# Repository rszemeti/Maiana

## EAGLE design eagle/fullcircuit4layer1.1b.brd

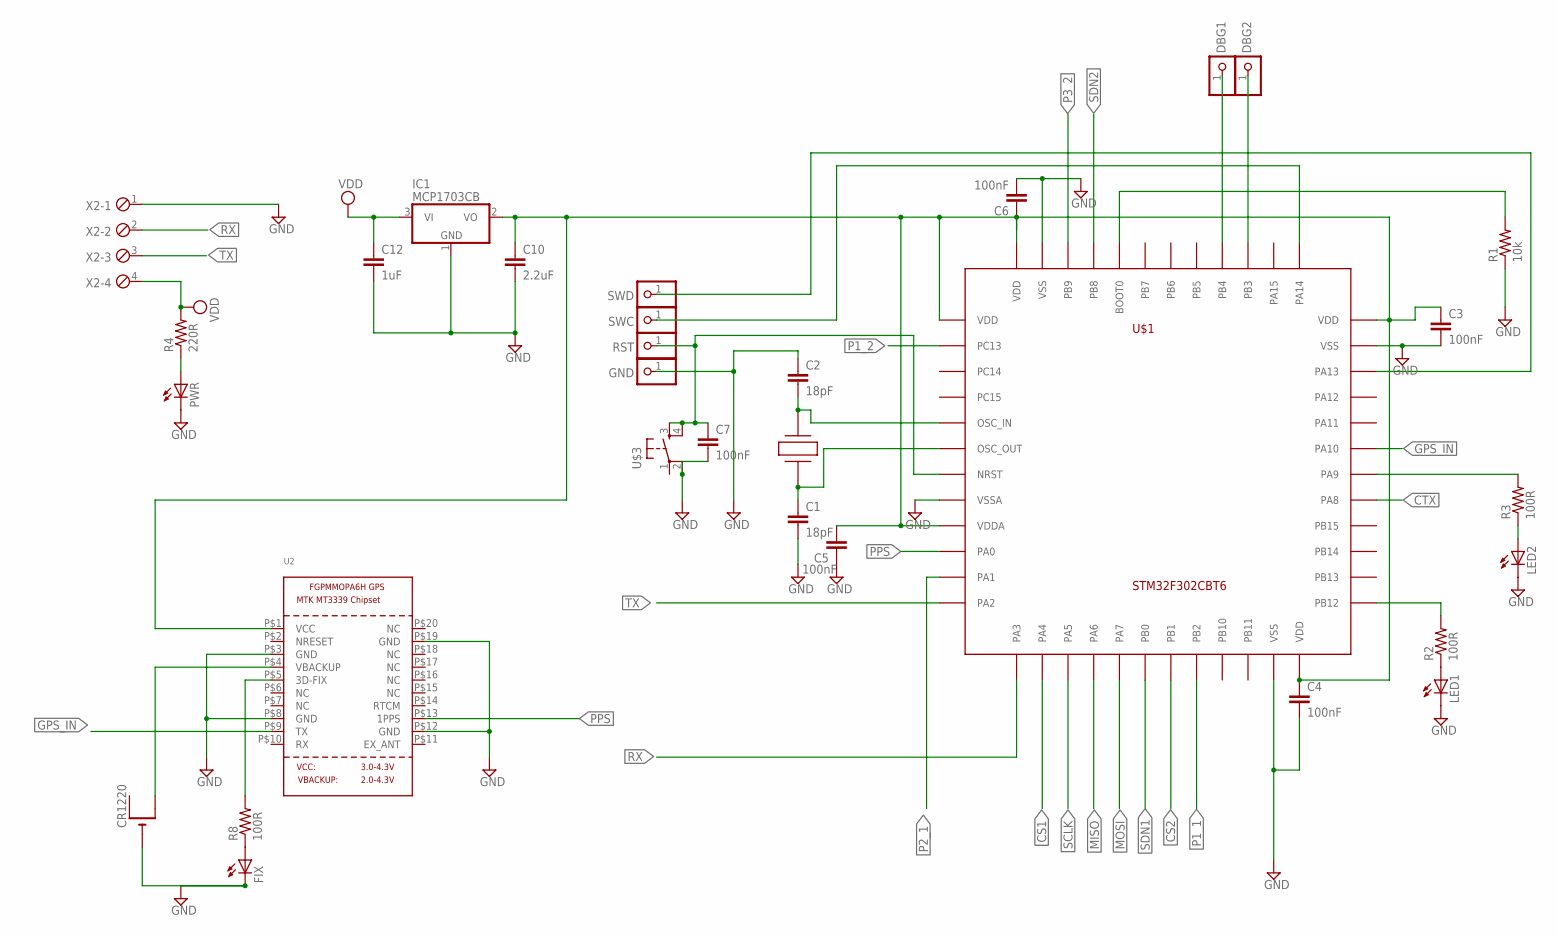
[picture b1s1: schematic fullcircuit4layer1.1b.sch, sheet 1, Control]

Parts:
C1, C2: 18pF; 0603-CAP
C3, C4, C5, C6, C7: 100nF; 0603-CAP
C10: 2.2uF; 0805
C12: 1uF; 0603-CAP
CR1220: CR1220SMT; CR1220-SMD
DBG1, DBG2: PINHD-1X1; 1X01
FIX: LEDCHIP-LED0603; CHIP-LED0603
GND: PINHD-1X1; 1X01
IC1: MCP1703CB; SOT23
LED1, LED2: LEDCHIP-LED0603; CHIP-LED0603
PWR: LEDCHIP-LED0603; CHIP-LED0603
R1: 10k; 0603-RES
R2, R3, R8: 100R; 0603-RES
R4: 220R; 0603-RES
RST: PINHD-1X1; 1X01
SWC: PINHD-1X1; 1X01
SWD: PINHD-1X1; 1X01
U2: GPS_FGPMMOPA6H; FGPMMOPA6H
U$1: STM32F302CBT6; LQFP48
U$3: TACTILE-SWITCH-7914G; 7914G
X1: TXC_7A
X2: MPT4; 4POL254

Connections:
CS1: U$1.P$14 (PA4); also elsewhere on the board
CS2: U$1.P$19 (PB1); also elsewhere on the board
CTX: U$1.P$29 (PA8); also elsewhere on the board
GND: C1.2, C2.1, C3.2, C4.2, C5.1, C6.2, C7.2, C10.2, C12.2, CR1220.-, FIX.C, GND.1, IC1.1 (GND), LED1.C, LED2.C, PWR.C, R1.1, U2.P$3 (GND), U2.P$8 (GND), U2.P$12 (GND), U2.P$19 (GND), U$1.P$8 (VSSA), U$1.P$23 (VSS), U$1.P$35 (VSS), U$1.P$47 (VSS), U$3.2, X2.1; also elsewhere on the board
GPS_IN: U2.P$9 (TX), U$1.P$31 (PA10)
MISO: U$1.P$16 (PA6); also elsewhere on the board
MOSI: U$1.P$17 (PA7); also elsewhere on the board
unnamed: R1.2, U$1.P$44 (BOOT0)
unnamed: SWC.1, U$1.P$37 (PA14)
unnamed: R2.2, U$1.P$25 (PB12)
unnamed: SWD.1, U$1.P$34 (PA13)
unnamed: C2.2, U$1.P$5 (OSC_IN), X1.P$2
unnamed: FIX.A, R8.1
unnamed: LED1.A, R2.1
unnamed: LED2.A, R3.1
unnamed: R3.2, U$1.P$30 (PA9)
unnamed: C1.1, U$1.P$6 (OSC_OUT), X1.P$1
unnamed: PWR.A, R4.1
unnamed: DBG2.1, U$1.P$39 (PB3)
unnamed: C3.1, C4.1, C5.2, C6.1, C10.1, IC1.2 (VO), U2.P$1 (VCC), U$1.P$1 (VDD), U$1.P$9 (VDDA), U$1.P$24 (VDD), U$1.P$36 (VDD), U$1.P$48 (VDD)
unnamed: DBG1.1, U$1.P$40 (PB4)
unnamed: R8.2, U2.P$5 (3D-FIX)
unnamed: CR1220.+$2 (+1), U2.P$4 (VBACKUP)
unnamed: C7.1, RST.1, U$1.P$7 (NRST), U$3.3, U$3.4
P1_1: U$1.P$20 (PB2); also elsewhere on the board
P1_2: U$1.P$2 (PC13); also elsewhere on the board
P2_1: U$1.P$11 (PA1); also elsewhere on the board
P3_2: U$1.P$46 (PB9); also elsewhere on the board
PPS: U2.P$13 (1PPS), U$1.P$10 (PA0)
RX: U$1.P$13 (PA3), X2.2
SCLK: U$1.P$15 (PA5); also elsewhere on the board
SDN1: U$1.P$18 (PB0); also elsewhere on the board
SDN2: U$1.P$45 (PB8); also elsewhere on the board
TX: U$1.P$12 (PA2), X2.3
VDD: C12.1, IC1.3 (VI), R4.2, X2.4; also elsewhere on the board

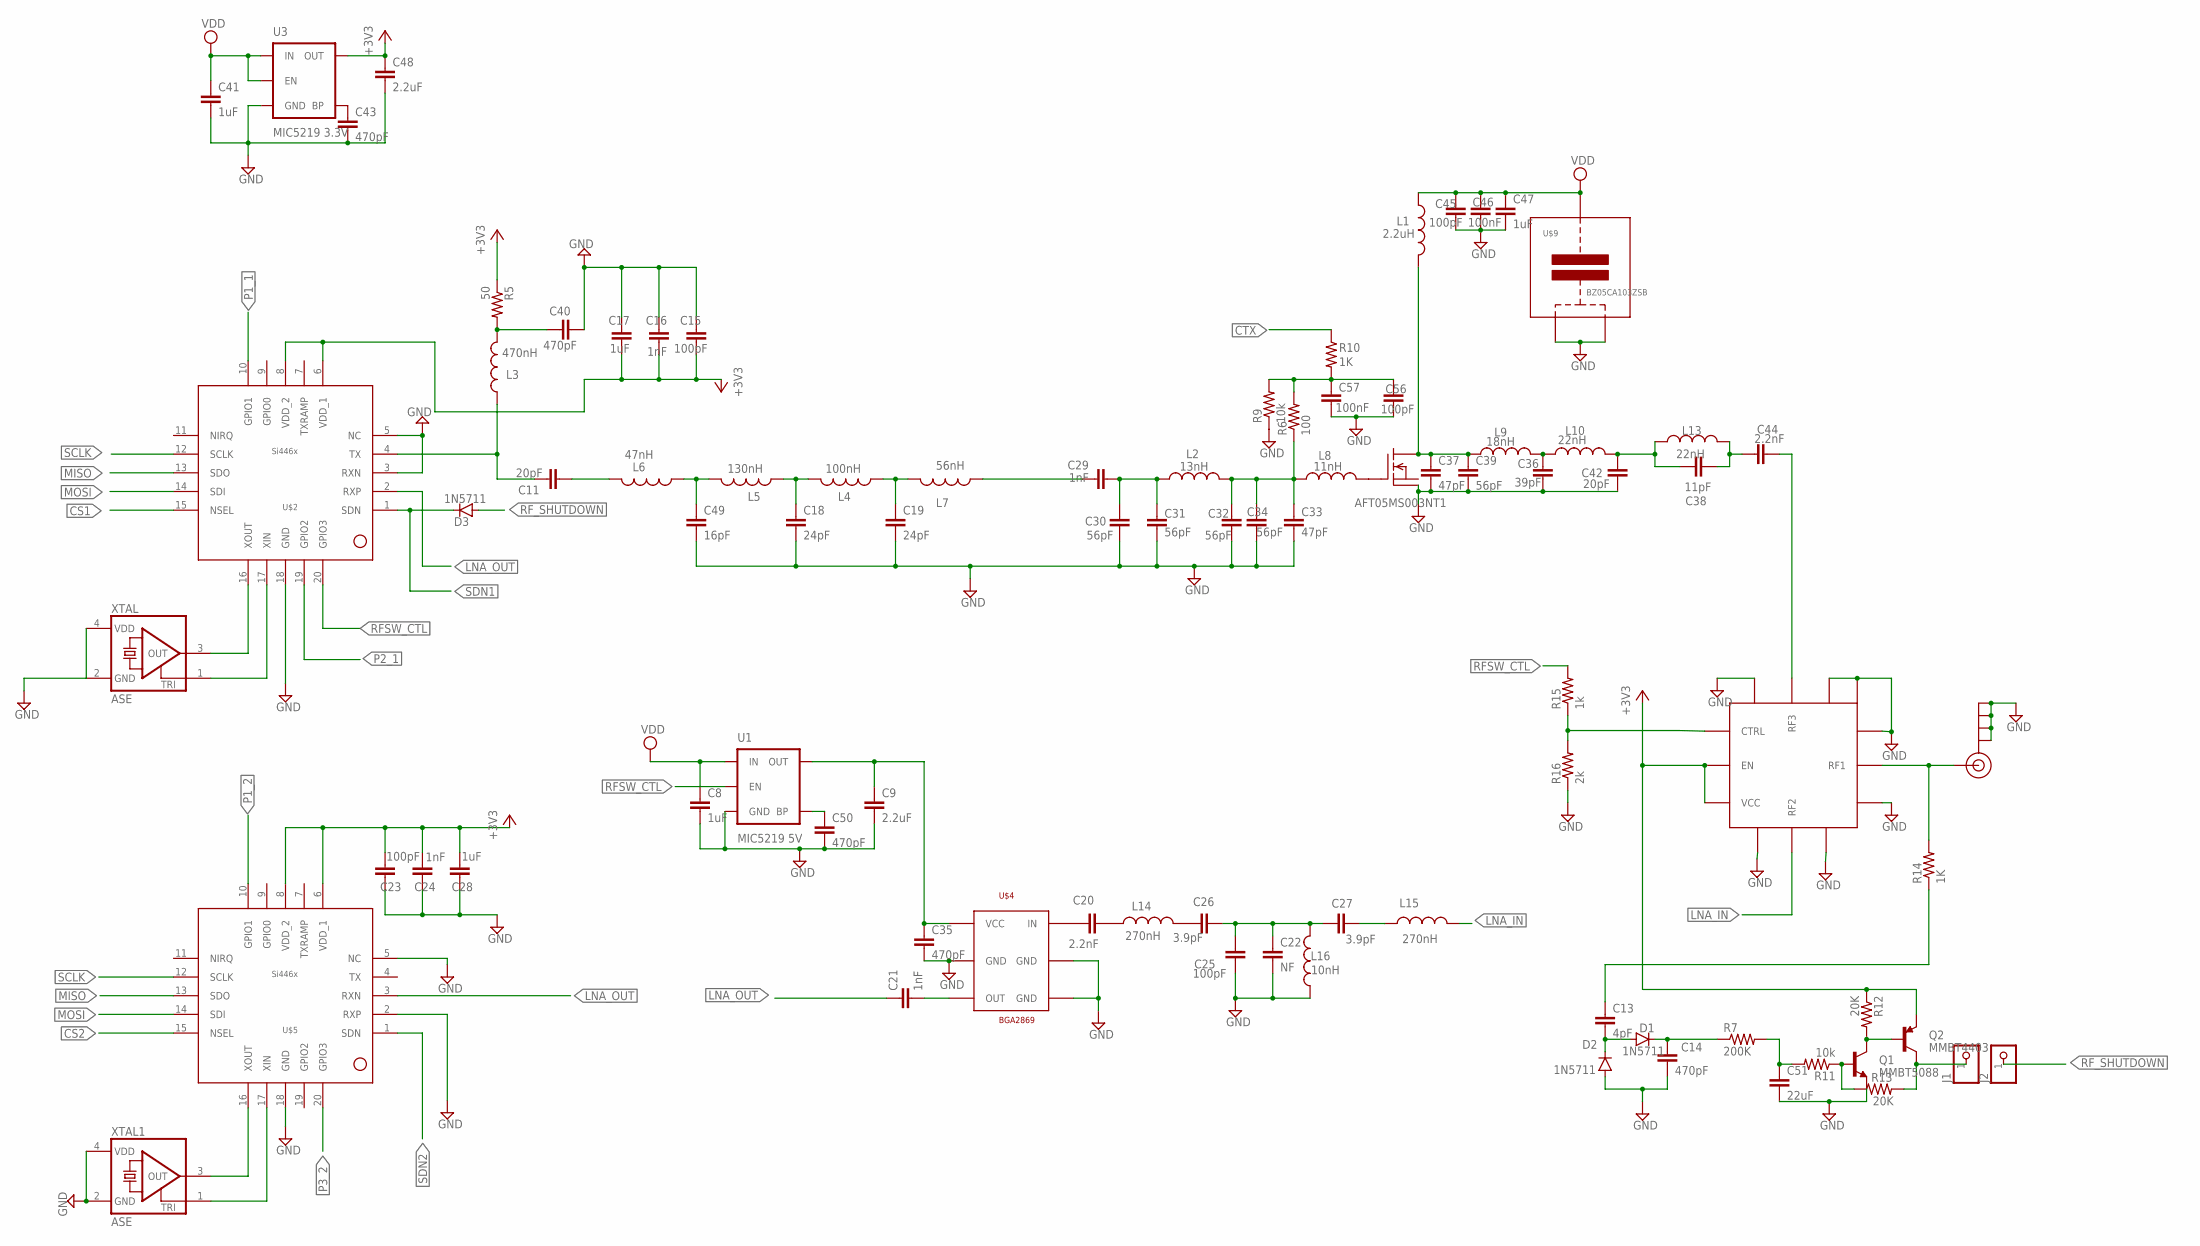
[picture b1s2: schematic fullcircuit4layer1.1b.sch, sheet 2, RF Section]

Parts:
C8, C17, C28, C41: 1uF; 0603-CAP
C9, C48: 2.2uF; 0603-CAP
C11: 20pF; 0603-CAP
C13: 4pF; 0603-CAP
C14, C35, C40, C43, C50: 470pF; 0603-CAP
C15, C23, C25, C56: 100pF; 0603-CAP
C16, C24: 1nF; 0603-CAP
C18, C19: 24pF; 0603-CAP
C20, C44: 2.2nF; 0805
C21, C29: 1nF; 0805
C22: NF; 0603-CAP
C26, C27: 3.9pF; 0603-CAP
C30, C31, C32, C34: 56pF; 0603-CAP
C33: 47pF; 0603-CAP
C36: 39pF; 0805
C37: 47pF; 0805
C38: 11pF; 0805
C39: 56pF; 0805
C42: 20pF; 0805
C45: 100pF; 0805
C46: 100nF; 0805
C47: 1uF; 0805
C49: 16pF; 0603-CAP
C51: 22uF; 0805
C57: 100nF; 0603-CAP
D1, D2, D3: 1N5711; SOD-123
J1, J2: PINHD-1X1; 1X01
J$1: SMA_EDGE; SMA-EDGE
L1: 2.2uH; 0805
L2: 13nH; 0603
L3: 470nH; 0805
L4: 100nH; 0603
L5: 130nH; 0603
L6: 47nH; 0603
L7: 56nH; 0603
L8: 11nH; 0603
L9: 18nH; 0805
L10, L13: 22nH; 0805
L14, L15: 270nH; 0603
L16: 10nH; 0603
Q1: MMBT5088; SOT23-3
Q2: MMBT4403; SOT23-3
R5: 50; 0603-RES
R6: 100; 0603-RES
R7: 200K; 0603-RES
R9, R11: 10k; 0603-RES
R10, R14: 1K; 0603-RES
R12, R13: 20K; 0603-RES
R15: 1k; 0603-RES
R16: 2k; 0603-RES
U1: MIC5219 5V; SOT23-5
U3: MIC5219 3.3V; SOT23-5
U$2, U$5: SI4463
U$4: BGA2869; SOT363
U$6: SKYWORKS-13330397LF; QFN12
U$7: AFT05MS003NT1; SOT-89
U$9: BZ05CA103ZSB; BZ05
XTAL, XTAL1: ASE

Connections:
+3V3: C15.1, C16.1, C17.1, C23.1, C24.1, C28.1, C48.1, Q2.2 (E), R5.1, R12.1, U3.5 (OUT), U$2.6 (VDD_1), U$2.8 (VDD_2), U$5.6 (VDD_1), U$5.8 (VDD_2), U$6.P$8 (EN), U$6.P$9 (VCC)
ANT: J$1.SIG (SIGNAL), R14.2, U$6.P$2 (RF1)
CS1: U$2.15 (NSEL); also elsewhere on the board
CS2: U$5.15 (NSEL); also elsewhere on the board
CTX: R10.1; also elsewhere on the board
GND: C8.2, C9.2, C14.2, C15.2, C16.2, C17.2, C18.2, C19.2, C22.2, C23.2, C24.2, C25.1, C28.2, C30.2, C31.2, C32.2, C33.2, C34.2, C35.2, C36.2, C37.2, C39.2, C40.2, C41.2, C42.2, C43.2, C45.2, C46.2, C47.2, C48.2, C49.2, C50.2, C51.2, C56.2, C57.2, D2.A, J$1.GND@0 (GND), J$1.GND@1 (GND), J$1.GND@2 (GND), J$1.GND@3 (GND), L16.1, Q1.2 (E), R9.1, R16.1, U1.2 (GND), U3.2 (GND), U$2.3 (RXN), U$2.5 (NC), U$2.18 (GND), U$4.2 (GND), U$4.4 (GND), U$4.5 (GND), U$5.2 (RXP), U$5.5 (NC), U$5.18 (GND), U$6.P$1 (GND), U$6.P$3 (GND), U$6.P$4 (GND), U$6.P$6 (GND), U$6.P$10 (GND), U$6.P$12 (GND), U$6.P$13 (GND), U$7.2@1 (PAD), U$9.P$1, U$9.P$2, XTAL.2 (GND), XTAL.4 (VDD), XTAL1.2 (GND), XTAL1.4 (VDD); also elsewhere on the board
LNAPWR: C9.1, C35.1, U1.5 (OUT), U$4.1 (VCC)
LNA_IN: L15.2, U$6.P$11 (RF2)
LNA_OUT: C21.1, U$2.2 (RXP), U$5.3 (RXN)
MISO: U$2.13 (SDO), U$5.13 (SDO); also elsewhere on the board
MOSI: U$2.14 (SDI), U$5.14 (SDI); also elsewhere on the board
unnamed: U$2.17 (XIN), XTAL.1 (TRI)
unnamed: C19.1, L4.1, L7.2
unnamed: C18.1, L4.2, L5.1
unnamed: C11.1, L3.1, U$2.4 (TX)
unnamed: C20.1, U$4.6 (IN)
unnamed: C21.2, U$4.3 (OUT)
unnamed: U$2.16 (XOUT), XTAL.3 (OUT)
unnamed: C20.2, L14.1
unnamed: C49.1, L5.2, L6.1
unnamed: C37.1, C39.1, L1.2, L9.1, U$7.3 (D)
unnamed: L8.2, U$7.1 (G)
unnamed: C32.1, C33.1, C34.1, L2.2, L8.1, R6.1
unnamed: C29.2, C30.1, C31.1, L2.1
unnamed: C36.1, L9.2, L10.1
unnamed: C38.1, C42.1, L10.2, L13.1
unnamed: C43.1, U3.4 (BP)
unnamed: C13.2, D1.A, D2.C
unnamed: C22.1, C25.2, C26.1, C27.2, L16.2
unnamed: C27.1, L15.1
unnamed: C26.2, L14.2
unnamed: C50.1, U1.4 (BP)
unnamed: U$5.17 (XIN), XTAL1.1 (TRI)
unnamed: U$5.16 (XOUT), XTAL1.3 (OUT)
unnamed: C14.1, D1.C, R7.1
unnamed: Q1.3 (C), Q2.1 (B), R12.2
unnamed: Q1.1 (B), R11.1, R13.1
unnamed: C38.2, C44.1, L13.2
unnamed: C51.1, R7.2, R11.2
unnamed: C11.2, L6.2
unnamed: C40.1, L3.2, R5.2
unnamed: C56.1, C57.1, R6.2, R9.2, R10.2
unnamed: C13.1, R14.1
P1_1: U$2.10 (GPIO1); also elsewhere on the board
P1_2: U$5.10 (GPIO1); also elsewhere on the board
P2_1: U$2.19 (GPIO2); also elsewhere on the board
P3_2: U$5.20 (GPIO3); also elsewhere on the board
PA_IN: C29.1, L7.1
PA_OUT: C44.2, U$6.P$5 (RF3)
RFSWCTL: R15.1, R16.2, U$6.P$7 (CTRL)
RFSW_CTL: R15.2, U1.3 (EN), U$2.20 (GPIO3)
RF_DETECT_LOGIC: J1.1, Q2.3 (C), R13.2
RF_SHUTDOWN: D3.A, J2.1
SCLK: U$2.12 (SCLK), U$5.12 (SCLK); also elsewhere on the board
SDN1: D3.C, U$2.1 (SDN); also elsewhere on the board
SDN2: U$5.1 (SDN); also elsewhere on the board
VDD: C8.1, C41.1, C45.1, C46.1, C47.1, L1.1, U1.1 (IN), U3.1 (IN), U3.3 (EN), U$9.P$3; also elsewhere on the board

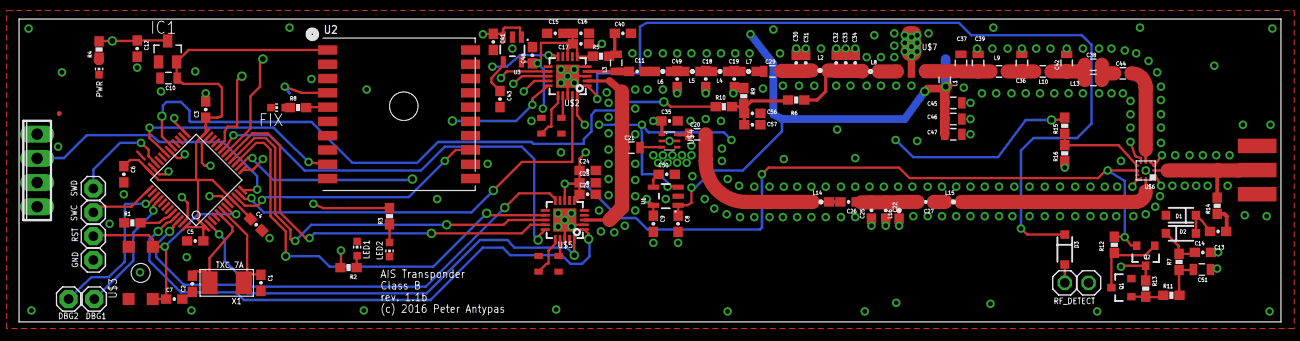
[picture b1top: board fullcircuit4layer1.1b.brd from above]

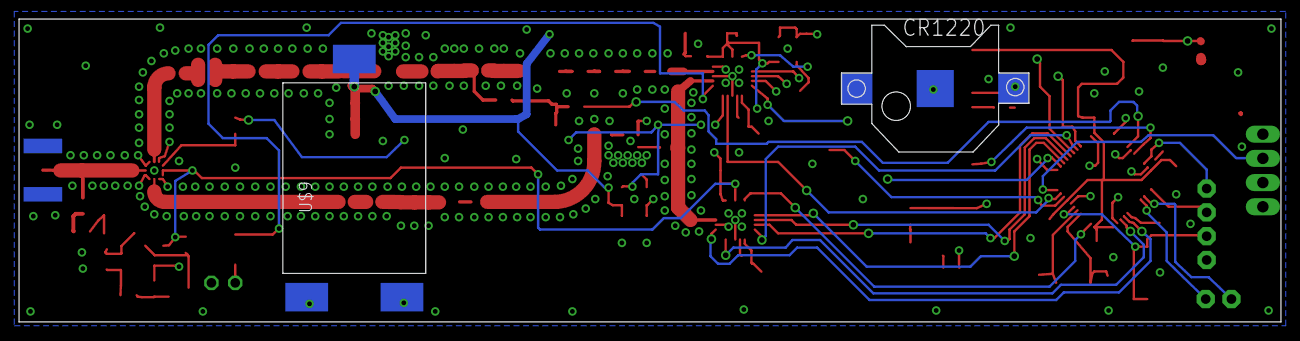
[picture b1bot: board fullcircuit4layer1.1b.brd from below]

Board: 4 copper layers, 132.5 x 31.8 mm, 118 parts (2 on the bottom side), 78 nets.

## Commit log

2020-04-11 updated schematic with missing values corrected PCB layout
2020-04-17 Corrected top cream layer for Si4463
2020-04-25 Changed LEDs and USART to match the PCB

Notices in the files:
eagle/fullcircuit4layer1.1b.brd:
(c) 2016 Peter Antypas
parts and their libraries:
SparkFun-Capacitors: Licensing: Creative Commons ShareAlike 4.0 International - https://creativecommons.org/licenses/by-sa/4.0
